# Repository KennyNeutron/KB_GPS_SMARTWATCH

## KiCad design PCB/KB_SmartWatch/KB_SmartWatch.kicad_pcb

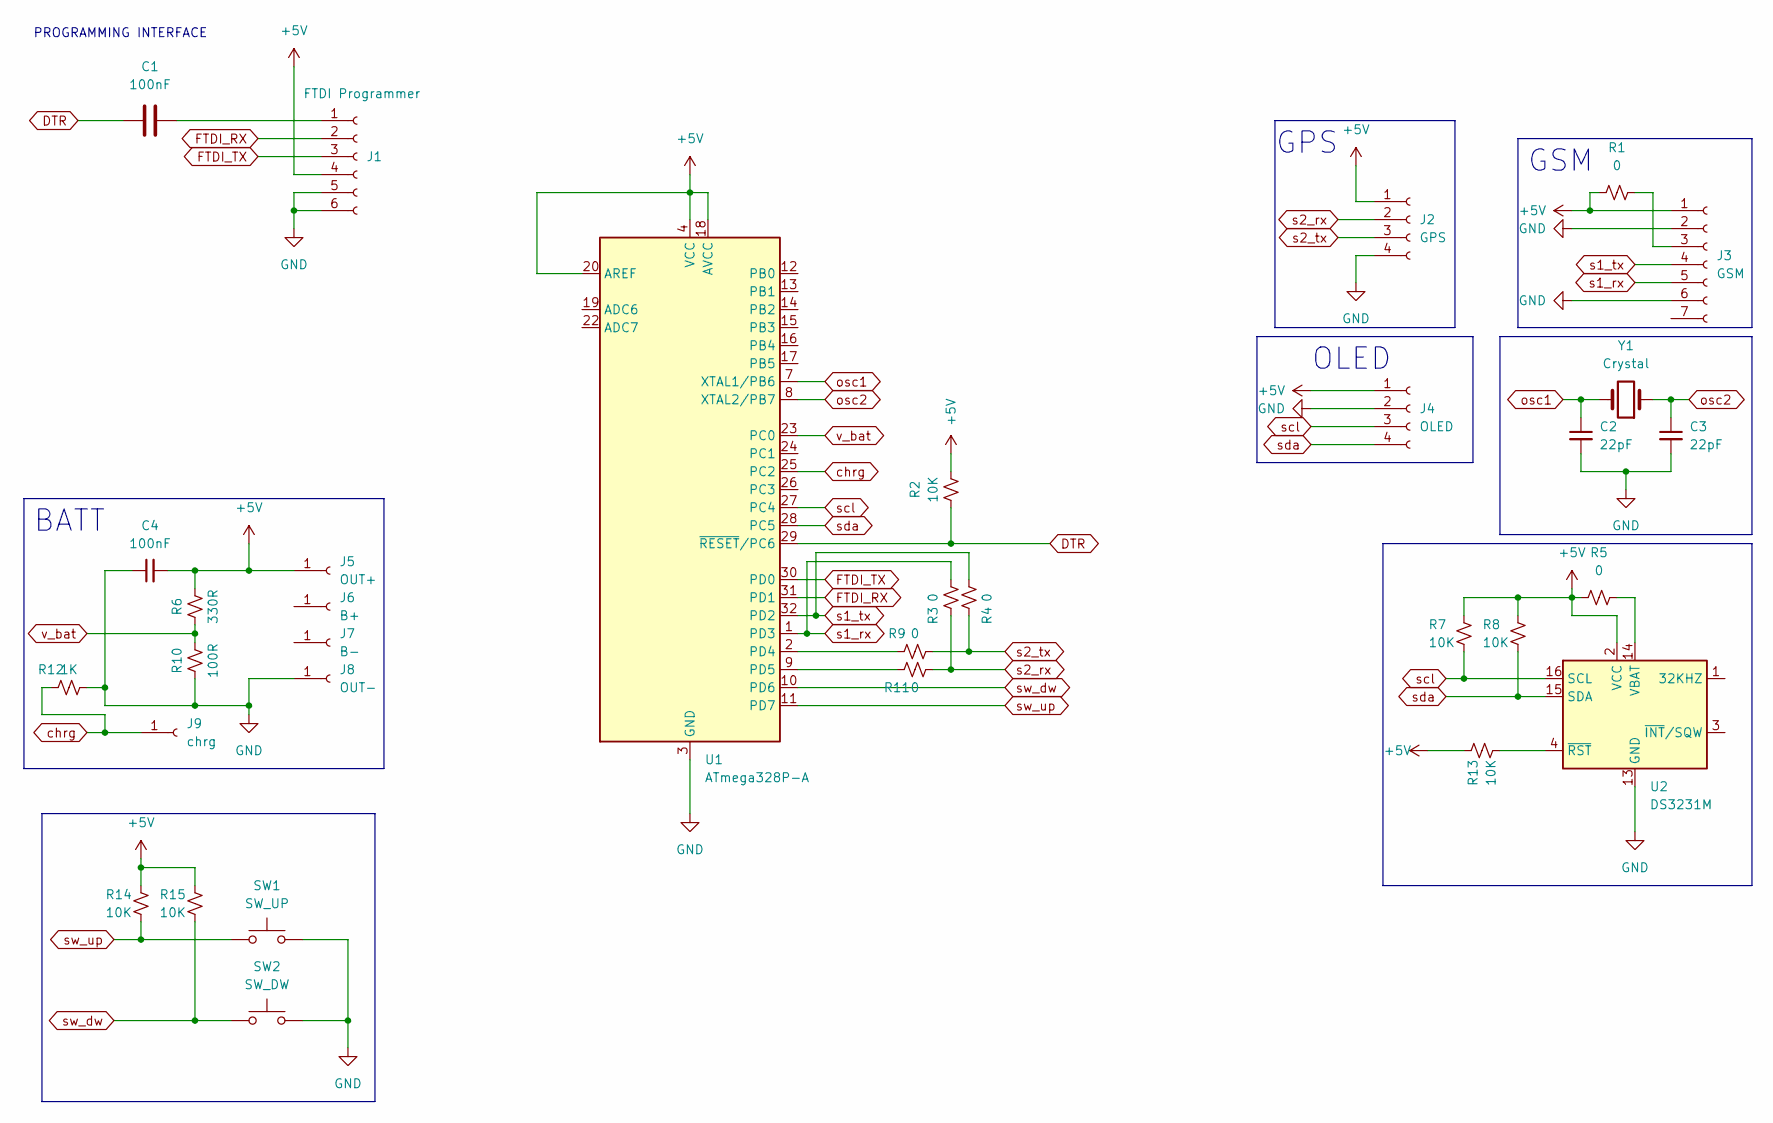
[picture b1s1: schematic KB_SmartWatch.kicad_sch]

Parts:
C1, C4: 100nF; C_1206_3216Metric_Pad1.33x1.80mm_HandSolder
C2, C3: 22pF; C_1206_3216Metric_Pad1.33x1.80mm_HandSolder
J1: FTDI Programmer; PinHeader_1x06_P2.54mm_Vertical
J2: GPS; PinHeader_1x04_P2.54mm_Vertical
J3: GSM; PinHeader_1x07_P2.54mm_Vertical
J4: OLED; PinHeader_1x04_P2.54mm_Vertical
J5: OUT+; PinHeader_1x01_P2.54mm_Vertical
J6: B+; PinHeader_1x01_P2.54mm_Vertical
J7: B-; PinHeader_1x01_P2.54mm_Vertical
J8: OUT-; PinHeader_1x01_P2.54mm_Vertical
J9: chrg; PinHeader_1x01_P2.54mm_Vertical
R1, R3, R4, R5, R9, R11: 0; R_0805_2012Metric_Pad1.20x1.40mm_HandSolder
R2, R7, R8, R13, R14, R15: 10K; R_0805_2012Metric_Pad1.20x1.40mm_HandSolder
R6: 330R; R_1206_3216Metric_Pad1.30x1.75mm_HandSolder
R10: 100R; R_1206_3216Metric_Pad1.30x1.75mm_HandSolder
R12: 1K; R_0805_2012Metric_Pad1.20x1.40mm_HandSolder
SW1: SW_UP; SW_PUSH_6mm_H4.3mm
SW2: SW_DW; SW_PUSH_6mm_H4.3mm
U1: ATmega328P-A; TQFP-32_7x7mm_P0.8mm
U2: DS3231M; SOIC-16W_7.5x10.3mm_P1.27mm
Y1: Crystal; Crystal_HC18-U_Vertical

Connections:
+5V: C4.2, J1.4, J2.1, J3.1, J4.1, J5.1, R1.1, R2.2, R5.1, R6.2, R7.2, R8.2, R13.2, R14.2, R15.2, U1.4 (VCC), U1.6 (VCC), U1.18 (AVCC), U1.20 (AREF), U2.2 (VCC)
DTR: C1.1, R2.1, U1.29 (~RESET/PC6)
FTDI_RX: J1.2, U1.31 (PD1)
FTDI_TX: J1.3, U1.30 (PD0)
GND: C2.2, C3.2, C4.1, J1.5, J1.6, J2.4, J3.2, J3.6, J4.2, J8.1, R10.1, R12.2, SW1.2, SW2.2, U1.3 (GND), U1.5 (GND), U1.21 (GND), U2.5 (GND), U2.6 (GND), U2.7 (GND), U2.8 (GND), U2.9 (GND), U2.10 (GND), U2.11 (GND), U2.12 (GND), U2.13 (GND)
unnamed: C1.2, J1.1
unnamed: J3.3, R1.2
unnamed: R5.2, U2.14 (VBAT)
unnamed: R9.1, U1.2 (PD4)
unnamed: R11.1, U1.9 (PD5)
unnamed: R13.1, U2.4 (~RST)
chrg: J9.1, R12.1, U1.25 (PC2)
osc1: C2.1, U1.7 (XTAL1/PB6), Y1.2
osc2: C3.1, U1.8 (XTAL2/PB7), Y1.1
s1_rx: J3.5, R3.2, U1.1 (PD3)
s1_tx: J3.4, R4.1, U1.32 (PD2)
s2_rx: J2.2, R3.1, R11.2
s2_tx: J2.3, R4.2, R9.2
scl: J4.3, R7.1, U1.27 (PC4), U2.16 (SCL)
sda: J4.4, R8.1, U1.28 (PC5), U2.15 (SDA)
sw_dw: R15.1, SW2.1, U1.10 (PD6)
sw_up: R14.1, SW1.1, U1.11 (PD7)
v_bat: R6.1, R10.2, U1.23 (PC0)

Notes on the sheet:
OLED
PROGRAMMING INTERFACE
BATT
GSM
GPS

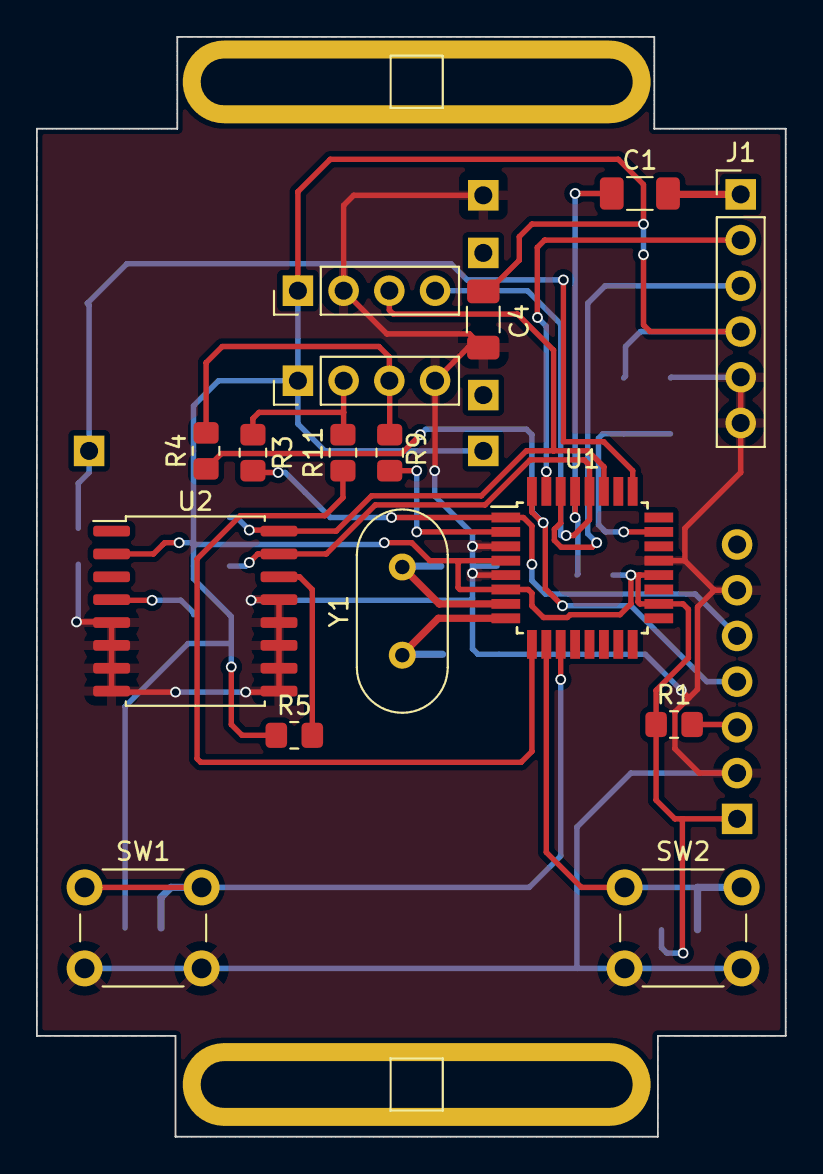
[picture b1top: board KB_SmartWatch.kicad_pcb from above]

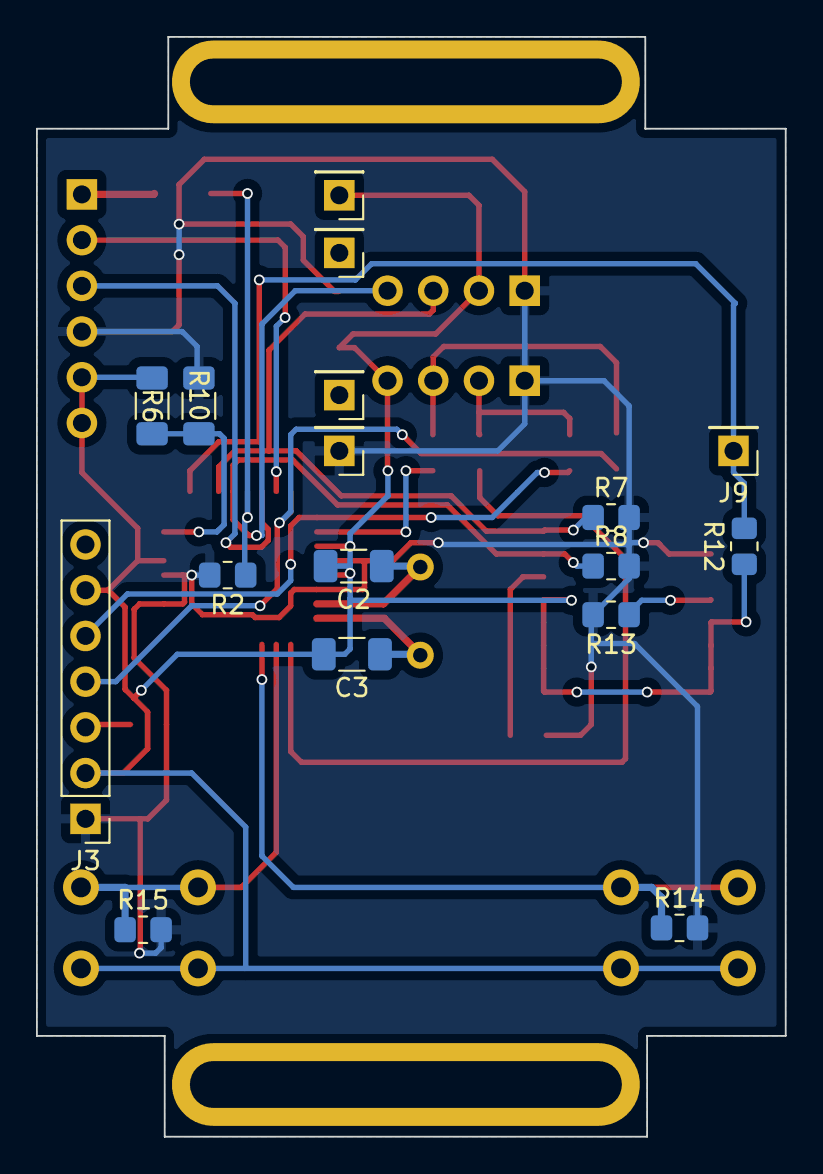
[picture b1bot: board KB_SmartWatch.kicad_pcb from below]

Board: 2 copper layers, 41.6 x 61.1 mm, 33 parts (17 on the bottom side), 23 nets.

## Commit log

2022-10-19 FIRST COMMIT: can now set TIME (time only not date yet)
2022-10-28 UPDATE: finished the pcb design
2022-11-12 UPDATE: smartwatch code working on OLED, RTC, and GSM module, message sending is working.
2022-11-12 UPDATE: code now works on sending the location (GPS and GSM), but a BUG: OLED doesn't display that message is sent
2022-11-16 UPDATE: working... NO custom recipient # yet... no INVALID location report via SMS
2022-11-16 UPDATE: working... now with INDVALID location report via SMS... NO custom recipient # yet...:
2022-12-01 UPDATE: DEC1 UPDATE
